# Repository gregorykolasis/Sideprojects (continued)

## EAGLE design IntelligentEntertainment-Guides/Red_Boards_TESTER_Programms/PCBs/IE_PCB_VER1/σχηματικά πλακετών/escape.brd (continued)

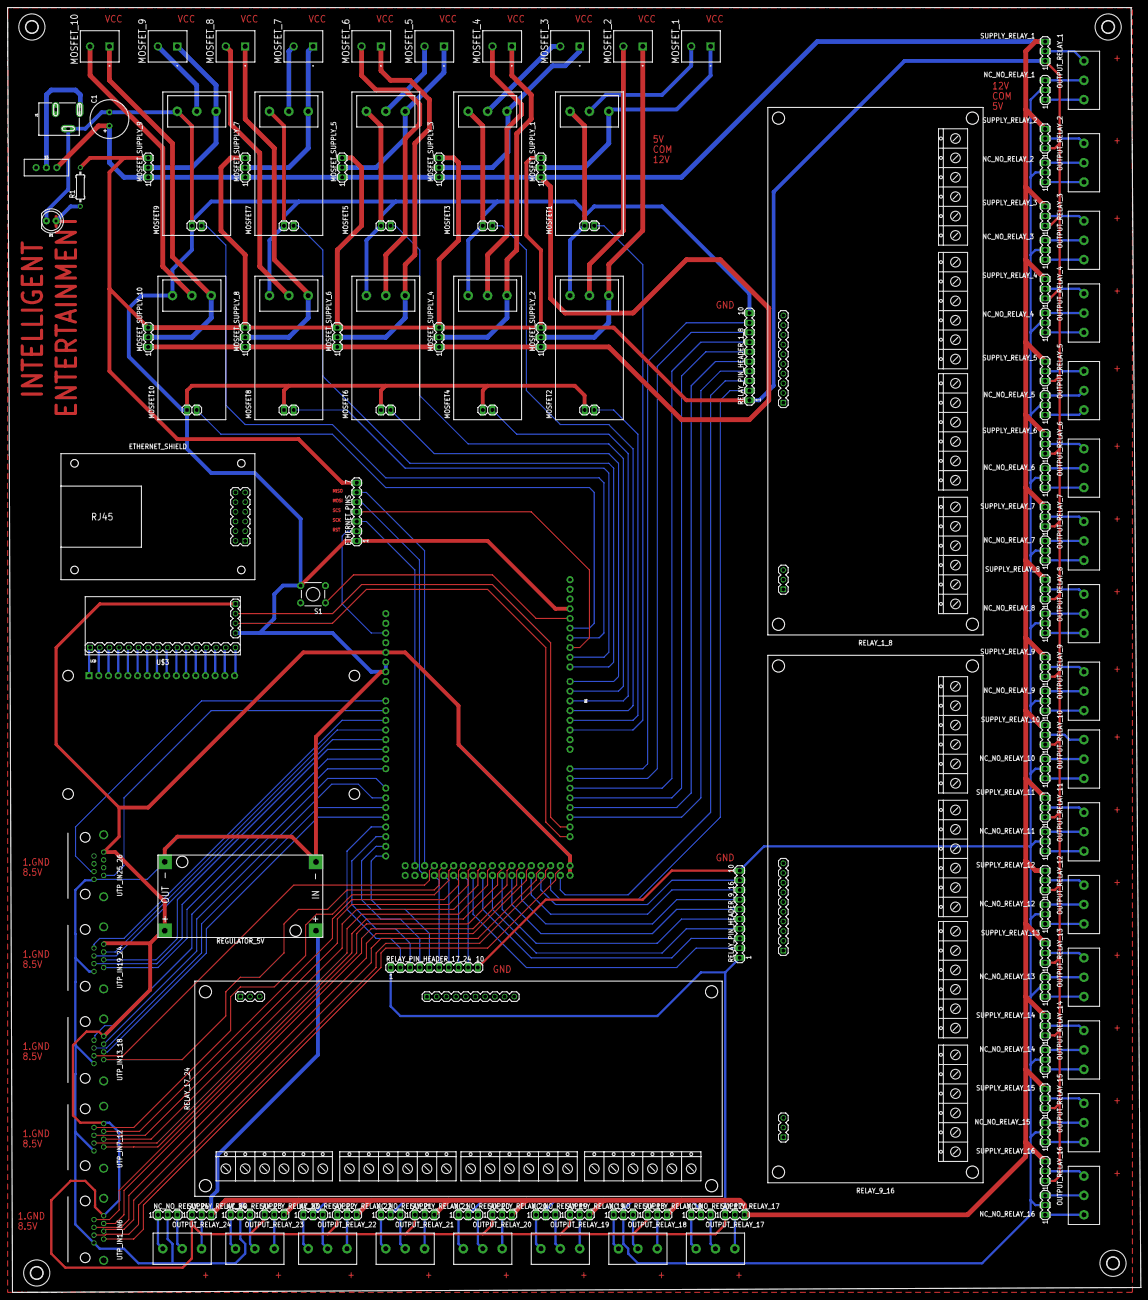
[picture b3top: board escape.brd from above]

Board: 2 copper layers, 296.9 x 336.5 mm, 129 parts (0 on the bottom side), 185 nets.

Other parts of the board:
U$1, U$2, U$4, U$5: 3,2

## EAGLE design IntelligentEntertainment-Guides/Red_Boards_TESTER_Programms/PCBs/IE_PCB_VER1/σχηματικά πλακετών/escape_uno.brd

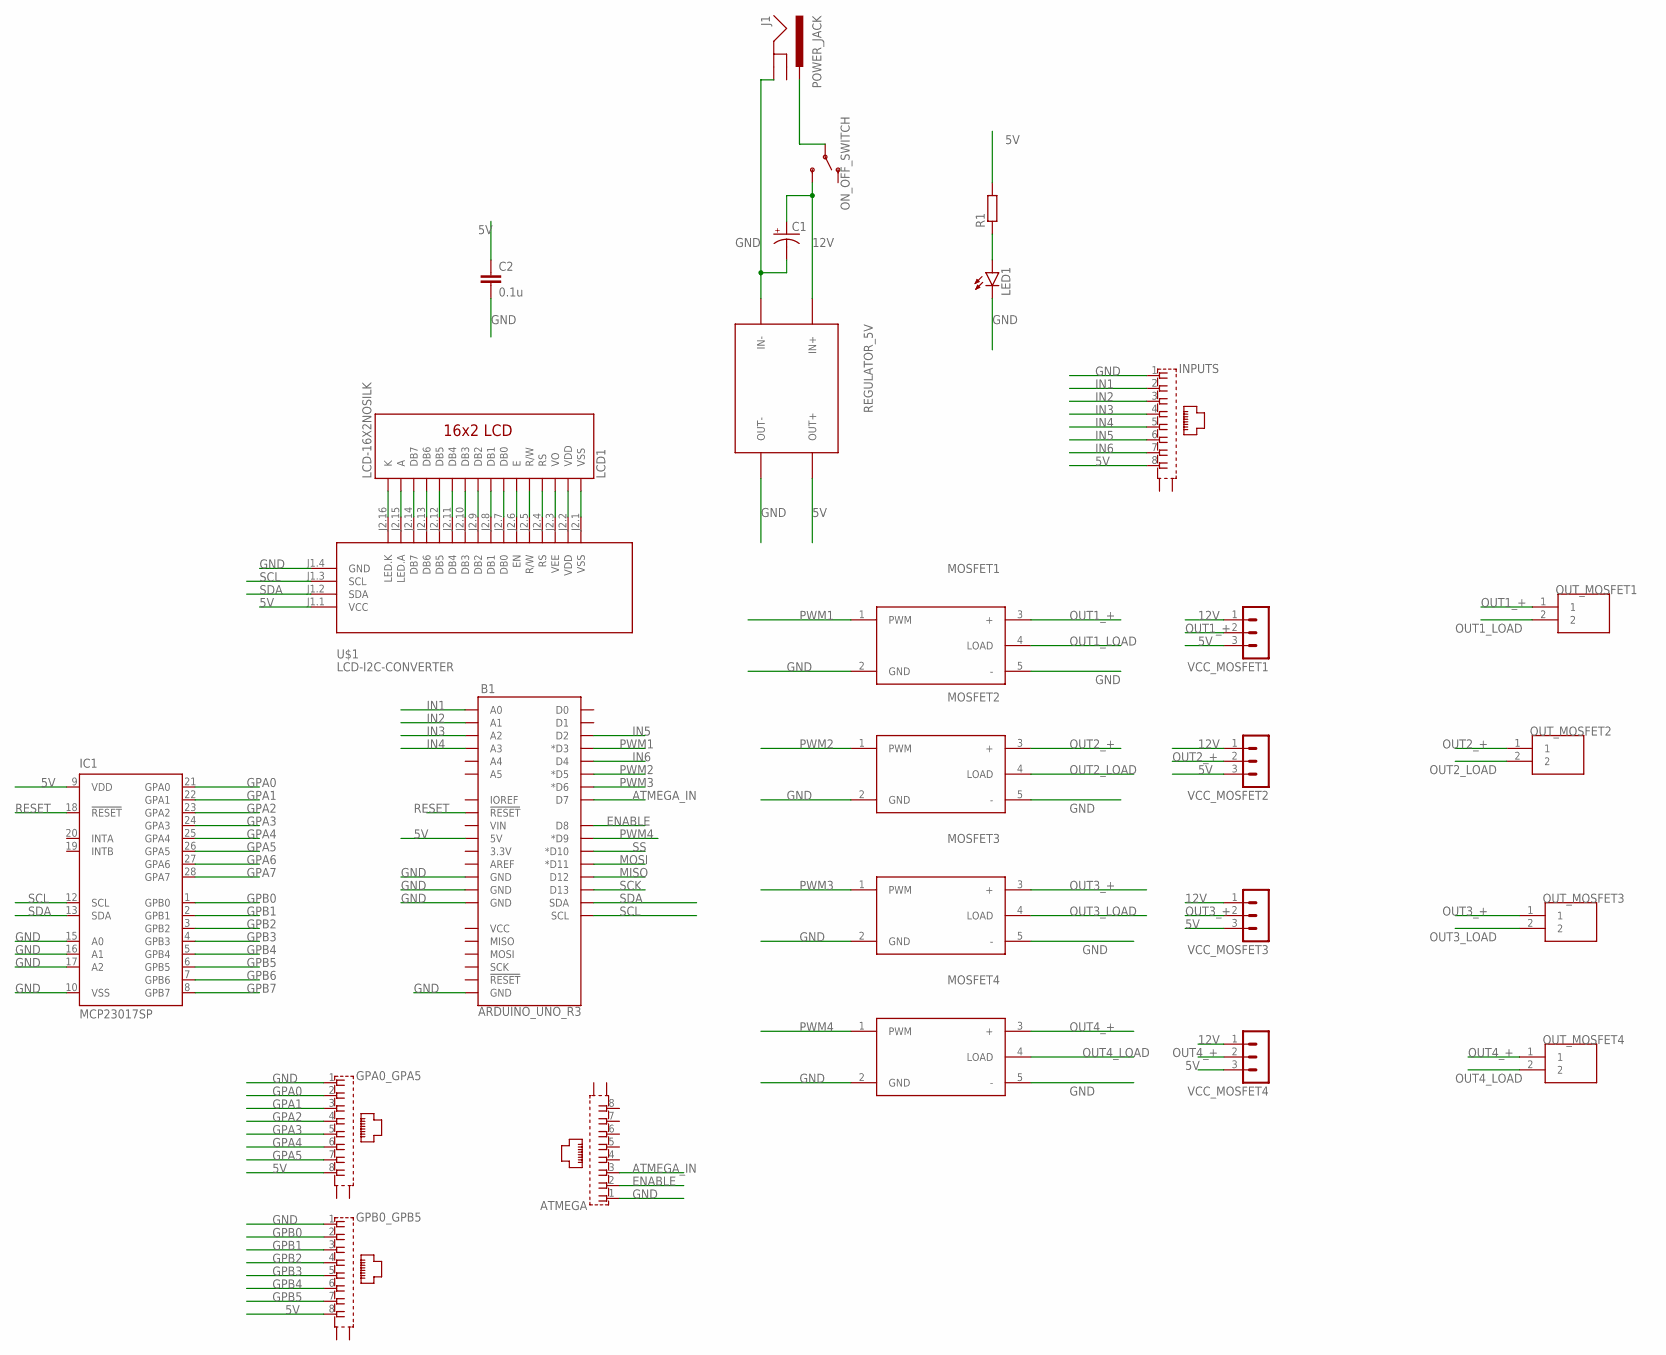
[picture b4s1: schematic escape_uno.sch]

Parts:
ATMEGA: GLX-S-88M
B1: ARDUINO_UNO_R3; ARDUINO_R3
C1: CPOL-USB45181C; B45181C
C2: 0.1u; C025-025X050
GPA0_GPA5: GLX-S-88M
GPB0_GPB5: GLX-S-88M
IC1: MCP23017SP; DIL28-3
INPUTS: GLX-S-88M
J1: POWER_JACK; POWER_JACK_PTH
LCD1: LCD-16X2NOSILK; LCD-16X2_NOSILK
LED1: LED5MM
MOSFET1, MOSFET2, MOSFET3, MOSFET4: SAMACSYS_PARTS_FR120N-ISOLATED-MOSFET-MOD
ON_OFF_SWITCH: SWITCH-SPDT-PTH-11.6X4.0MM-SHORT_LEADS; SWITCH_SPDT_PTH_11.6X4.0MM
OUT_MOSFET1, OUT_MOSFET2, OUT_MOSFET3, OUT_MOSFET4: TB006-508-02BE_TB006-508-02BE; TB006-508-02BE_CUI_TB006-508-02BE
R1: R-EU_0207/10; 0207/10
REGULATOR_5V: DIY-MODULES_DC-DC-STEP-DOWN-LM2596
U$1: LCD-I2C-CONVERTER
VCC_MOSFET1, VCC_MOSFET2, VCC_MOSFET3, VCC_MOSFET4: MA03-1

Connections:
5V: B1.5V, C2.1, GPA0_GPA5.8, GPB0_GPB5.8, IC1.9 (VDD), INPUTS.8, R1.2, REGULATOR_5V.OUT+, U$1.J1.1 (VCC), VCC_MOSFET1.3, VCC_MOSFET2.3, VCC_MOSFET3.3, VCC_MOSFET4.3
12V: C1.+, ON_OFF_SWITCH.3 (S), REGULATOR_5V.IN+, VCC_MOSFET1.1, VCC_MOSFET2.1, VCC_MOSFET3.1, VCC_MOSFET4.1
ATMEGA_IN: ATMEGA.3, B1.D7
ENABLE: ATMEGA.2, B1.D8
GND: ATMEGA.1, B1.GND@1 (GND), B1.GND@2 (GND), B1.GND@3 (GND), B1.GND@4 (GND), C1.-, C2.2, GPA0_GPA5.1, GPB0_GPB5.1, IC1.10 (VSS), IC1.15 (A0), IC1.16 (A1), IC1.17 (A2), INPUTS.1, J1.GND, LED1.K (C), MOSFET1.2 (GND), MOSFET1.5 (-), MOSFET2.2 (GND), MOSFET2.5 (-), MOSFET3.2 (GND), MOSFET3.5 (-), MOSFET4.2 (GND), MOSFET4.5 (-), REGULATOR_5V.IN-, REGULATOR_5V.OUT-, U$1.J1.4 (GND)
GPA0: GPA0_GPA5.2, IC1.21 (GPA0)
GPA1: GPA0_GPA5.3, IC1.22 (GPA1)
GPA2: GPA0_GPA5.4, IC1.23 (GPA2)
GPA3: GPA0_GPA5.5, IC1.24 (GPA3)
GPA4: GPA0_GPA5.6, IC1.25 (GPA4)
GPA5: GPA0_GPA5.7, IC1.26 (GPA5)
GPA6: IC1.27 (GPA6)
GPA7: IC1.28 (GPA7)
GPB0: GPB0_GPB5.2, IC1.1 (GPB0)
GPB1: GPB0_GPB5.3, IC1.2 (GPB1)
GPB2: GPB0_GPB5.4, IC1.3 (GPB2)
GPB3: GPB0_GPB5.5, IC1.4 (GPB3)
GPB4: GPB0_GPB5.6, IC1.5 (GPB4)
GPB5: GPB0_GPB5.7, IC1.6 (GPB5)
GPB6: IC1.7 (GPB6)
GPB7: IC1.8 (GPB7)
IN1: B1.A0, INPUTS.2
IN2: B1.A1, INPUTS.3
IN3: B1.A2, INPUTS.4
IN4: B1.A3, INPUTS.5
IN5: B1.D2, INPUTS.6
IN6: B1.D4, INPUTS.7
MISO: B1.D12
MOSI: B1.D11 (*D11)
unnamed: J1.PWR, ON_OFF_SWITCH.2
unnamed: LED1.A, R1.1
unnamed: LCD1.16 (K), U$1.J2.16 (LED.K)
unnamed: LCD1.15 (A), U$1.J2.15 (LED.A)
unnamed: LCD1.14 (DB7), U$1.J2.14 (DB7)
unnamed: LCD1.13 (DB6), U$1.J2.13 (DB6)
unnamed: LCD1.12 (DB5), U$1.J2.12 (DB5)
unnamed: LCD1.11 (DB4), U$1.J2.11 (DB4)
unnamed: LCD1.10 (DB3), U$1.J2.10 (DB3)
unnamed: LCD1.9 (DB2), U$1.J2.9 (DB2)
unnamed: LCD1.8 (DB1), U$1.J2.8 (DB1)
unnamed: LCD1.7 (DB0), U$1.J2.7 (DB0)
unnamed: LCD1.6 (E), U$1.J2.6 (EN)
unnamed: LCD1.5 (R/W), U$1.J2.5 (R/W)
unnamed: LCD1.4 (RS), U$1.J2.4 (RS)
unnamed: LCD1.3 (VO), U$1.J2.3 (VEE)
unnamed: LCD1.2 (VDD), U$1.J2.2 (VDD)
unnamed: LCD1.1 (VSS), U$1.J2.1 (VSS)
OUT1_+: MOSFET1.3 (+), OUT_MOSFET1.1, VCC_MOSFET1.2
OUT1_LOAD: MOSFET1.4 (LOAD), OUT_MOSFET1.2
OUT2_+: MOSFET2.3 (+), OUT_MOSFET2.1, VCC_MOSFET2.2
OUT2_LOAD: MOSFET2.4 (LOAD), OUT_MOSFET2.2
OUT3_+: MOSFET3.3 (+), OUT_MOSFET3.1, VCC_MOSFET3.2
OUT3_LOAD: MOSFET3.4 (LOAD), OUT_MOSFET3.2
OUT4_+: MOSFET4.3 (+), OUT_MOSFET4.1, VCC_MOSFET4.2
OUT4_LOAD: MOSFET4.4 (LOAD), OUT_MOSFET4.2
PWM1: B1.D3 (*D3), MOSFET1.1 (PWM)
PWM2: B1.D5 (*D5), MOSFET2.1 (PWM)
PWM3: B1.D6 (*D6), MOSFET3.1 (PWM)
PWM4: B1.D9 (*D9), MOSFET4.1 (PWM)
RESET: B1.RESET@1 (!RESET!), IC1.18 (!RESET)
SCK: B1.D13
SCL: B1.SCL, IC1.12 (SCL), U$1.J1.3 (SCL)
SDA: B1.SDA, IC1.13 (SDA), U$1.J1.2 (SDA)
SS: B1.D10 (*D10)

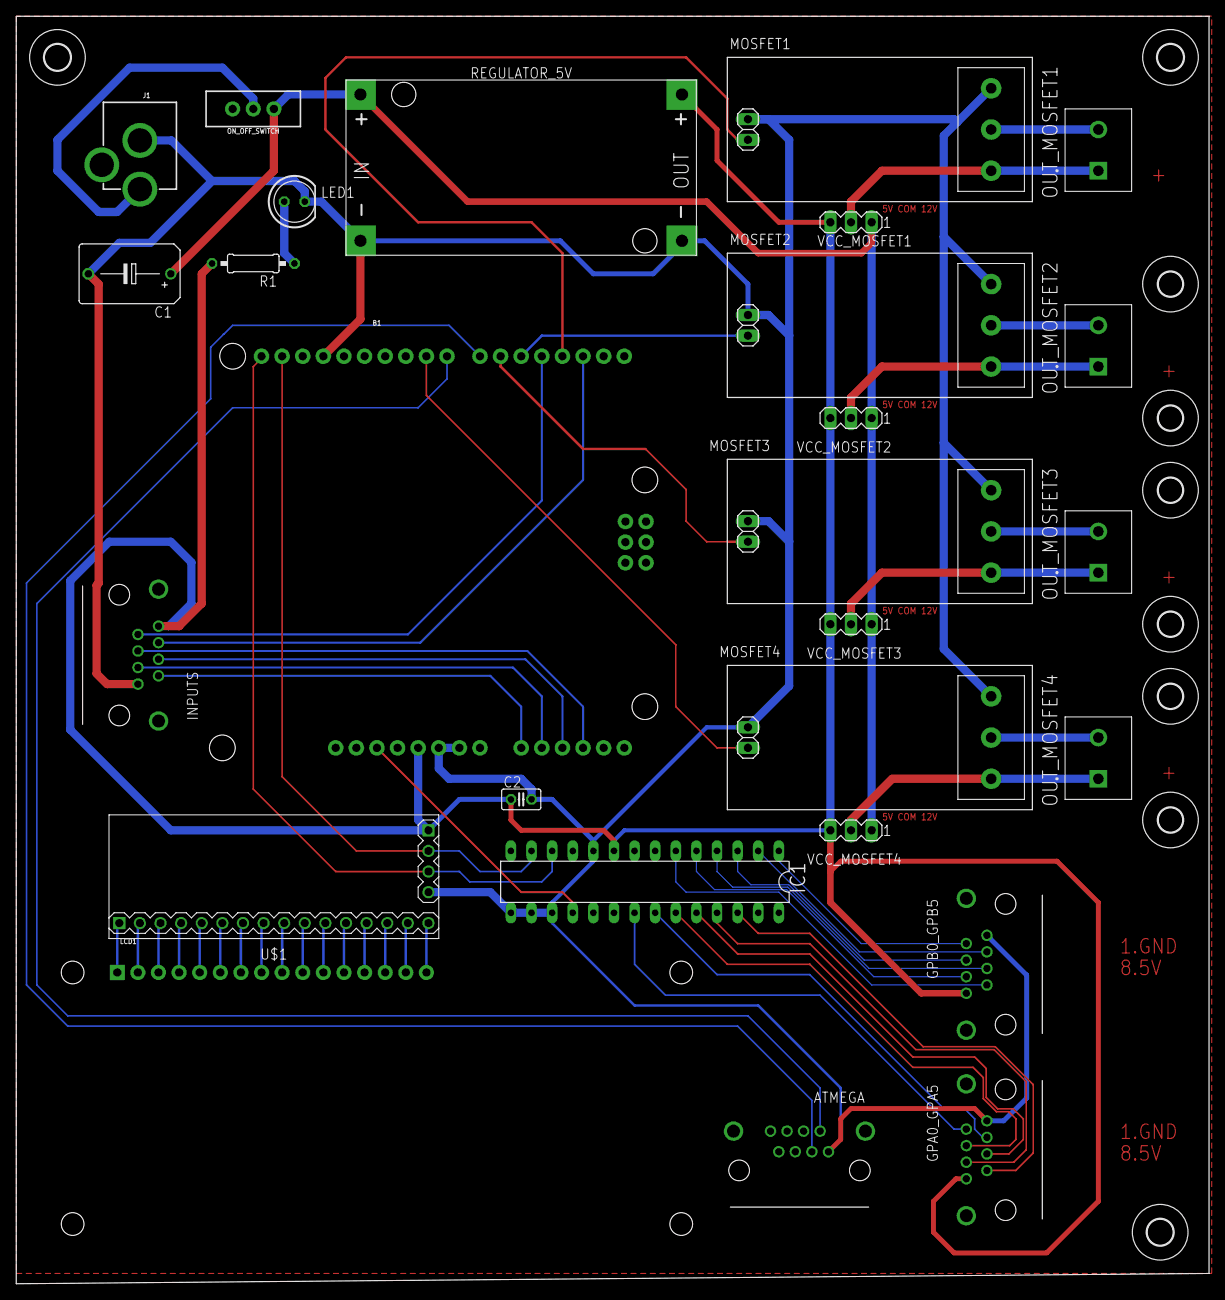
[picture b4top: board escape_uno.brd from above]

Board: 2 copper layers, 147.0 x 156.2 mm, 36 parts (0 on the bottom side), 56 nets.

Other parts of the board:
U$2, U$3, U$4, U$5, U$6, U$7: 3,0
U$9, U$10, U$11: 3,2

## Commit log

2024-04-30 1st Commit
    1st Commit
2024-05-03 Dimitris openProgramsAtStartup Monitor
    Dimitris openProgramsAtStartup Monitor
2024-05-10 Updated sideProjects including Anydesk_Utils
    Updated sideProjects including Anydesk_Utils
2024-05-14 Backend Deployer / monitorStartup
    Backend Deployer / monitorStartup
2024-05-14 monitorStartup fix
    monitorStartup fix
2024-06-04 Updates
    Updates
2024-06-05 LicensedExpired when Customers dont pay
    LicensedExpired when Customers dont pay
2024-06-19 Symantec Ghost Image fix GPT
    Symantec Ghost Image fix GPT
2024-08-01 Updates GPT_Walkthrough
    Updates GPT_Walkthrough
2024-08-01 Update Guide
    Update Guide
2024-09-17 Updates Ghosting Usage
    Updates Ghosting Usage
2024-10-01 Intelligent Guides
    Intelligent Guides
2024-10-01 Guide to Upgrade the RPI to accept new Software
    Guide to Upgrade the RPI to accept new Software
2024-10-01 ESP32 Programmer
    ESP32 Programmer
2024-10-02 Guide to Convert old RED-PCB to Master Slaves
    Guide to Convert old RED-PCB to Master Slaves
2024-10-04 AF_Database_Queries , Connection-Photos-Electronics
    AF_Database_Queries , Connection-Photos-Electronics
2024-10-07 Ask for CSV Export
    Ask for CSV Export
2024-10-07 Updates for Guides
    Updates for Guides
2024-10-18 Old Boards & Testers
    Old Boards & Testers
2024-11-13 PCB Scanner 125Khz
    PCB Scanner 125Khz
2024-11-26 New Software Installation on Old Mindtrap Image
    New Software Installation on Old Mindtrap Image
2024-12-13 Mindtrap Old Code Refactor like Rostock
    Mindtrap Old Code Refactor like Rostock
2025-01-02 All Programmers
    All Programmers
2025-01-16 Network Scanner and some Reworks
    Network Scanner and some Reworks
2025-01-20 Ghost-Images-Notes-Evolution
    Ghost-Images-Notes-Evolution
2025-01-31 125Khz_Rfid_Checker
    125Khz_Rfid_Checker
2025-01-31 RS485 Programmer
    RS485 Programmer
2025-03-05 Improved Wol , RS485 Updated by config.ini
    Improved Wol , RS485 Updated by config.ini
